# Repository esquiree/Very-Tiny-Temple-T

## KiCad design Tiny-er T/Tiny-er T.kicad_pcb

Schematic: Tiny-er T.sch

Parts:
C1: 1uF; C_0805
D1, D2, D3, D4, D5, D6, D7, D8, D9, D10, D11, D12, D13, D14, D15, D16, D17, D18, D19, D20, D21, D22, D23, D24, D25, D26, D27, D28, D29, D30, D31, D32, D33, D34, D35, D36, D37, D38: LED; LED_0805
J1: Conn_01x02; BK913nosilk
J2: Conn_02x04_Counter_Clockwise; Pin_Header_Straight_2x04_Pitch1.27mm
POWER0: SW_SPST; SW_SPDT_PCM12
R1: 1K; R_0805
SW1: SW_SPST; SW_SPST_EVPBF
U1: ATtiny85-20SU; ATtiny85_SMD
U2, U3, U4, U5, U6: 74HC595; QFN50P250X350X100-17N

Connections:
CLK: J2.3, U1.3 (XTAL2/PB4), U2.11, U3.11, U4.11, U5.11, U6.11
DATA: J2.6, U1.6 (PB1), U2.14
GND: C1.2, D1.1, D2.1, D3.1, D4.1, D5.1, D6.1, D7.1, D8.1, D9.1, D10.1, D11.1, D12.1, D13.1, D14.1, D15.1, D16.1, D17.1, D18.1, D19.1, D20.1, D21.1, D22.1, D23.1, D24.1, D25.1, D26.1, D27.1, D28.1, D29.1, D30.1, D31.1, D32.1, D33.1, D34.1, D35.1, D36.1, D37.1, D38.1, J1.1, J2.4, SW1.2, U1.4 (GND), U2.8, U3.8, U4.8, U5.8, U6.8
unnamed: D1.2, U2.15
unnamed: D2.2, U2.1
unnamed: D3.2, U2.2
unnamed: D4.2, U2.3
unnamed: D5.2, U2.4
unnamed: D6.2, U2.5
unnamed: D7.2, U2.6
unnamed: D8.2, U2.7
unnamed: D9.2, U3.15
unnamed: D10.2, U3.1
unnamed: D11.2, U3.2
unnamed: D12.2, U3.3
unnamed: D13.2, U3.4
unnamed: D14.2, U3.5
unnamed: D15.2, U3.6
unnamed: D16.2, U3.7
unnamed: D17.2, U4.15
unnamed: D18.2, U4.1
unnamed: D19.2, U4.2
unnamed: D20.2, U4.3
unnamed: D21.2, U4.4
unnamed: D22.2, U4.5
unnamed: D23.2, U4.6
unnamed: D24.2, U4.7
unnamed: D25.2, U5.15
unnamed: D26.2, U5.1
unnamed: D27.2, U5.2
unnamed: D28.2, U5.3
unnamed: D29.2, U5.4
unnamed: D30.2, U5.5
unnamed: D31.2, U5.6
unnamed: D32.2, U5.7
unnamed: D33.2, U6.15
unnamed: D34.2, U6.1
unnamed: D35.2, U6.2
unnamed: D36.2, U6.3
unnamed: D37.2, U6.4
unnamed: D38.2, U6.5
unnamed: J1.2, POWER0.2
unnamed: U2.9, U3.14
unnamed: U3.9, U4.14
unnamed: U4.9, U5.14
unnamed: U5.9, U6.14
OE: J2.7, U1.7 (PB2), U2.13, U3.13, U4.13, U5.13, U6.13
REG: J2.2, U1.2 (XTAL1/PB3), U2.12, U3.12, U4.12, U5.12, U6.12
RST: J2.1, R1.2, U1.1 (~RESET~/PB5)
SW1: J2.5, SW1.1, U1.5 (AREF/PB0)
VCC: C1.1, J2.8, POWER0.1, R1.1, U1.8 (VCC), U2.10, U2.16, U3.10, U3.16, U4.10, U4.16, U5.10, U5.16, U6.10, U6.16

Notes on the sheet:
Tiny-er T
8 JUN 2019
1.1

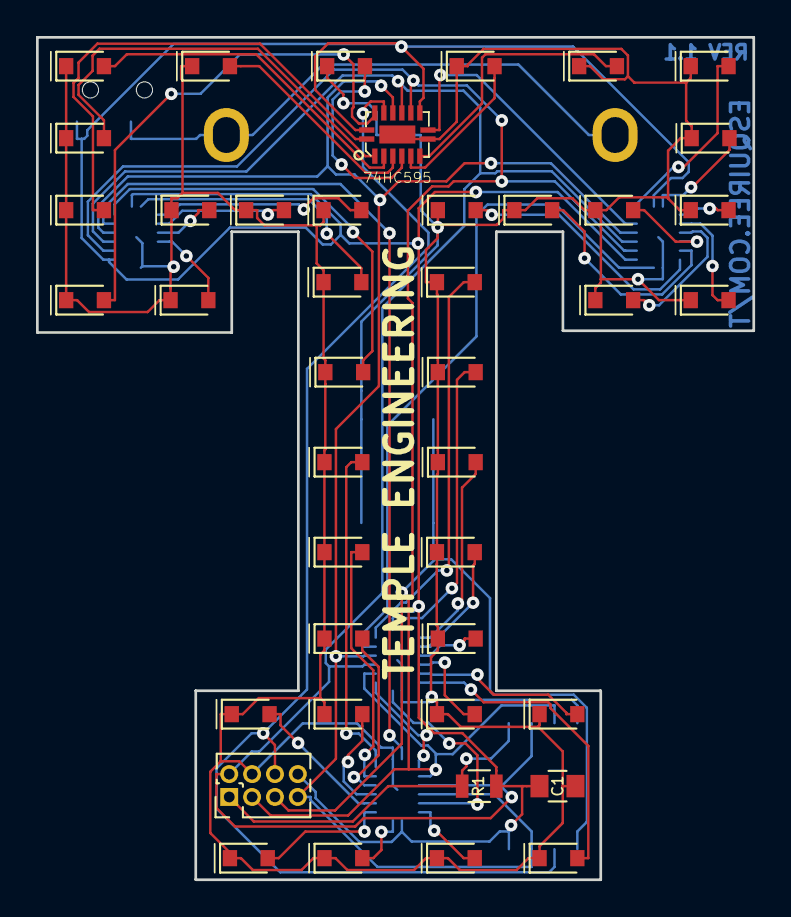
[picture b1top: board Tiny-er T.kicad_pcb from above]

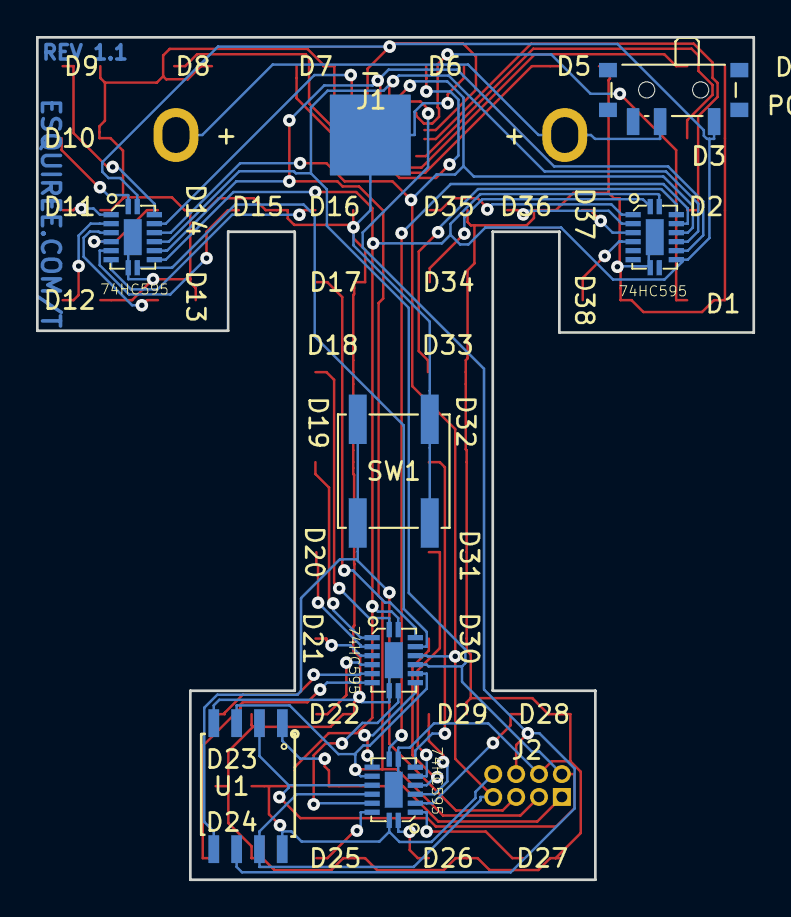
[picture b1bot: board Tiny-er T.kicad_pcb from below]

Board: 2 copper layers, 39.8 x 46.8 mm, 50 parts (8 on the bottom side), 51 nets.

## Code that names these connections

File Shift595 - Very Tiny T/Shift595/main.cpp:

#include <avr/io.h>
#define F_CPU 16000000UL
#include <util/delay.h>
#include <avr/interrupt.h>
#include <avr/eeprom.h>
#include <avr/sleep.h>

#define HC595_PORT   PORTB
#define HC595_DDR    DDRB

#define BTN_PIN PB0
#define HC595_DS_POS PB1      //Data pin (DS) pin location
#define HC595_SH_CP_POS PB4      //Shift Clock (SH_CP) pin location
#define HC595_ST_CP_POS PB3      //Store Clock (ST_CP) pin location
#define HC595_OE PB2			//Output Enable

uint8_t mode = 0;
uint8_t j = 0;

uint64_t line_pattern1[] = {0x7800000, 0x18600000, 0x20100000, 0x40080000, 0x80040000,  0X100020000, 0X2200011801, 0X1C0000E402, 0X0000000204, 0X00000001F8 };
uint64_t line_pattern2[] = {0x7800000, 0x1FE00000, 0x3FF00000, 0x7FF80000, 0xFFFC0000,  0x1FFFE0000, 0x23FFFF1801, 0x3FFFFFFC03, 0x3FFFFFFE07, 0x3FFFFFFFFF };		
	
void HC595Init()
{
   //Make the Data(DS), Shift clock (SH_CP), Store Clock (ST_CP) lines output
   HC595_DDR |= ((1<<HC595_SH_CP_POS)|(1<<HC595_ST_CP_POS)|(1<<HC595_DS_POS)|(1<<HC595_OE));
   HC595_PORT |= (1<<HC595_PORT);

}

#define HC595DataHigh() (HC595_PORT|=(1<<HC595_DS_POS))
#define HC595DataLow() (HC595_PORT&=(~(1<<HC595_DS_POS)))

void HC595Pulse()
{
   //Pulse the Shift Clock
   HC595_PORT|=(1<<HC595_SH_CP_POS);//HIGH

   HC595_PORT&=(~(1<<HC595_SH_CP_POS));//LOW
}


void HC595Latch()
{
   HC595_PORT|=(1<<HC595_ST_CP_POS);//HIGH
   _delay_us(1);

   HC595_PORT&=(~(1<<HC595_ST_CP_POS));//LOW
   _delay_us(1);
}


void HC595Write(uint8_t data)
{
   for(uint8_t i=0;i<8;i++)
   {

      if(data & 0b10000000)
      {
         HC595DataHigh();
      }
      else
      {
         HC595DataLow();
      }
      HC595Pulse();  //Pulse the Clock line
      data=data<<1;  //Now bring next bit at MSB position
   }
}


void Wait()
{
   _delay_ms(150);
}

void Wait2()
{
	_delay_us(10);
}



void write5Bytes(uint8_t byte0, uint8_t byte1, uint8_t byte2, uint8_t byte3, uint8_t byte4)
{
	
	//uint8_t temp = byte2;
	//byte2 = (byte2 & 0x0F) | ((byte2>>1) & (0x70)) | ((byte2<<3) & (0x80));
	HC595Write(byte4);
	HC595Write(byte3);
	HC595Write(byte2);
	HC595Write(byte1);
	HC595Write(byte0);
	HC595Latch();
}

void EEPROM_write(uint8_t uiAddress, uint8_t ucData) //Stolen from https://stackoverflow.com/questions/4412111/avr-eeprom-read-write
{
	while(EECR & (1<<EEPE));    /* Wait for completion of previous write */
	EEARH = 0x00;
	EEARL = uiAddress;
	EEDR = ucData;
	cli();
	EECR |= (1<<EEMPE);     /* Write logical one to EEMPE */
	EECR |= (1<<EEPE);      /* Start eeprom write by setting EEPE */
	sei();
}
unsigned char EEPROM_read(uint8_t uiAddress) //Stolen from https://stackoverflow.com/questions/4412111/avr-eeprom-read-write
{
	while(EECR & (1<<EEPE)); /* Wait for completion of previous write */

	EEARH = (uiAddress>>8);  /* Set up address register */
	EEARL = uiAddress;

	EECR |= (1<<EERE);       /* Start eeprom read by writing EERE */

	return EEDR;             /* Return data from Data Register */
}


ISR(PCINT0_vect)
{
	_delay_ms(1);
	if (((PINB&(1<<BTN_PIN)) == 0x00))
	{
		sleep_disable();
		mode++;
		j = 0xFD; //Exit current mode loop
		if (mode >= 9){ //Max mode options - 1
			mode = 0;
		}
	}
}


int main()
{
	

	HC595Init();
	
	PORTB |= (1<<BTN_PIN); //Btn pull up enable
	mode = EEPROM_read(0x07); // Read mode selection from last power cycle
	if(mode > 0x09){ //catch any errors in EEPROM
		mode = 0x00;
	}
	
	//PRR = (1<<PRTIM0) | (1<<PRTIM1) | (1<<PRUSI) | (1<<PRADC); //power reduction
	GIMSK |= (1<<PCIE);
	PCMSK |= (1<<BTN_PIN);
	sei();
		  
	while(1)
	{	
		if (mode == 0)
		{
			for (j=0;j<10;j++)
			{
				write5Bytes(line_pattern1[j],line_pattern1[j]>>8,line_pattern1[j]>>16,line_pattern1[j]>>24,line_pattern1[j]>>32);
				//data_byte = data_byte<<1;
				Wait();   	
				Wait();	 
				Wait();				
			}
		}
		if (mode == 1)
		{
			for (j=0;j<10;j++)
			{
				write5Bytes(line_pattern2[j],line_pattern2[j]>>8,line_pattern2[j]>>16,line_pattern2[j]>>24,line_pattern2[j]>>32);
				//data_byte = data_byte<<1;
				Wait();
				Wait();
			}
			
			for (j=10;j>0;j--)
			{
				if (mode == 1) //Check for exit condition
				{
					write5Bytes(line_pattern2[j-1],line_pattern2[j-1]>>8,line_pattern2[j-1]>>16,line_pattern2[j-1]>>24,line_pattern2[j-1]>>32);
					//data_byte = data_byte<<1;
					Wait();
					Wait();
				}
			}
					
		}
		if (mode == 2)
		{
			uint64_t shiftedNum =0x01;
			for (j=0;j<38;j++)
			{
				write5Bytes(shiftedNum,shiftedNum>>8,shiftedNum>>16,shiftedNum>>24,shiftedNum>>32);
				shiftedNum = shiftedNum<<1;				   
				Wait();										
			}
		}
		if (mode == 3)
		{
			uint64_t shiftedNum =0x00;
			for (j=0;j<39;j++)
			{
				write5Bytes(shiftedNum,shiftedNum>>8,shiftedNum>>16,shiftedNum>>24,shiftedNum>>32);
				shiftedNum = shiftedNum<<1;
				shiftedNum = shiftedNum + 1;				   
				Wait();										
			}
			if (mode == 3)//check for exit condition
			{
				for (j=0;j<39;j++)
				{
					write5Bytes(shiftedNum,shiftedNum>>8,shiftedNum>>16,shiftedNum>>24,shiftedNum>>32);
					shiftedNum = shiftedNum<<1;
					Wait();
				}
			}			
		}
		if (mode == 4)
		{
			uint64_t shiftedNum =0x0F;
			while (mode == 4)
			{
				write5Bytes(shiftedNum,shiftedNum>>8,shiftedNum>>16,shiftedNum>>24,shiftedNum>>32);
				if ((shiftedNum & 0x002000000000) == 0x002000000000) //Bit at end
				{
					shiftedNum = shiftedNum<<1;
					shiftedNum = shiftedNum + 1;
				} 
				else
				{
					shiftedNum = shiftedNum<<1;
				}
				
				Wait();
			}
		}
		if (mode == 5)
		{
			uint64_t shiftedNum =0x00;
			for (shiftedNum=0;mode == 5;shiftedNum++)
			{
				write5Bytes(shiftedNum,shiftedNum>>8,shiftedNum>>16,shiftedNum>>24,shiftedNum>>32);
				Wait2();
			}
		}
		if (mode == 6)
		{
			write5Bytes(0xFF,0xFF,0xFF,0xFF,0xFF);
			_delay_ms(1000);
		}
		if (mode == 7)
		{
			mode = 0; //skip this mode
			write5Bytes(0,0,0,0,0);
			sleep_enable();
			sleep_cpu();
						
		}
		if (mode == 8)
		{
			//This mode is also skipped
			write5Bytes(0xFF,0xFF,0xFF,0xFF,0xFF);
			_delay_ms(1000);
		}
			 	 
	}
}

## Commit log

2019-10-22 Program Files
2019-10-22 KICAD FILES
